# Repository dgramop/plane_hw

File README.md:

# Plane Hardware

Board Design Rev1 Mistakes:
- Wrong footprint for the PX4 connector on the pitot. Accidentally used the same one as all the I2C busses. Already have these connectors
- Forgot to order MALE connectors that go on the board. JST female is the for the cable. Whoops

Rev 2 Wishlist:
- Better harnessing - fewer things to connect + better modularity. Then we can have test beds for each part in isolation

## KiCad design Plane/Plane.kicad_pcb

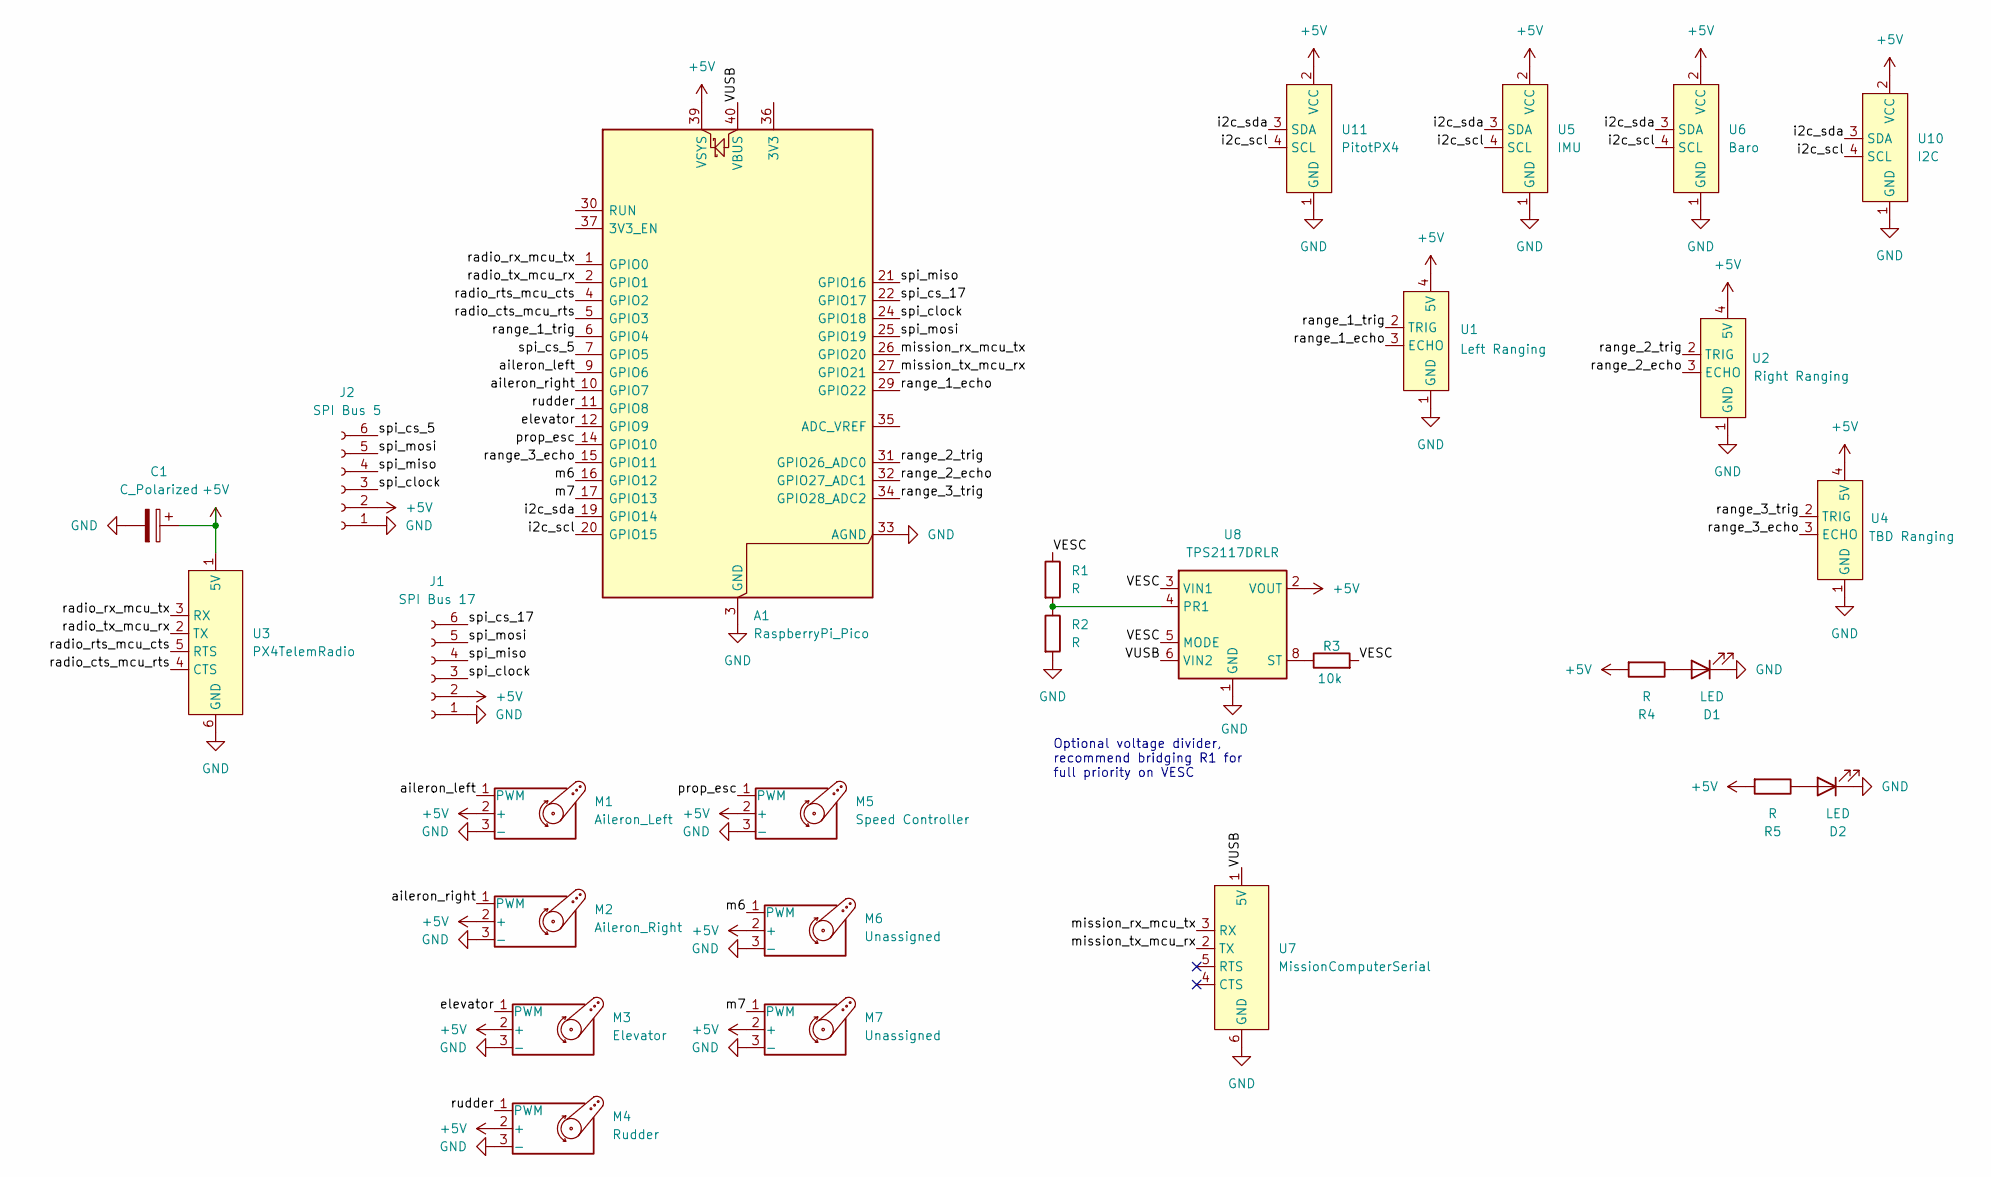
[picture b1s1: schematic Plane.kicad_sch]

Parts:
A1: RaspberryPi_Pico; RaspberryPi_Pico_Common_Unspecified
C1: C_Polarized; CP_Radial_D6.3mm_P2.50mm
D1, D2: LED; JST_PH_B2B-PH-K_1x02_P2.00mm_Vertical
J1: SPI Bus 17; JST_PH_B6B-PH-K_1x06_P2.00mm_Vertical
J2: SPI Bus 5; JST_PH_B6B-PH-K_1x06_P2.00mm_Vertical
M1: Aileron_Left; JST_PH_B3B-PH-K_1x03_P2.00mm_Vertical
M2: Aileron_Right; JST_PH_B3B-PH-K_1x03_P2.00mm_Vertical
M3: Elevator; JST_PH_B3B-PH-K_1x03_P2.00mm_Vertical
M4: Rudder; JST_PH_B3B-PH-K_1x03_P2.00mm_Vertical
M5: Speed Controller; JST_PH_B3B-PH-K_1x03_P2.00mm_Vertical
M6, M7: Unassigned; JST_PH_B3B-PH-K_1x03_P2.00mm_Vertical
R1, R2, R4, R5: R; R_0805_2012Metric_Pad1.20x1.40mm_HandSolder
R3: 10k; R_0805_2012Metric_Pad1.20x1.40mm_HandSolder
U1: Left Ranging; JST_PH_B4B-PH-K_1x04_P2.00mm_Vertical
U2: Right Ranging; JST_PH_B4B-PH-K_1x04_P2.00mm_Vertical
U3: PX4TelemRadio; JST_GH_SM06B-GHS-TB_1x06-1MP_P1.25mm_Horizontal
U4: TBD Ranging; JST_PH_B4B-PH-K_1x04_P2.00mm_Vertical
U5: IMU; JST_PH_B4B-PH-K_1x04_P2.00mm_Vertical
U6: Baro; JST_PH_B4B-PH-K_1x04_P2.00mm_Vertical
U7: MissionComputerSerial; JST_GH_SM06B-GHS-TB_1x06-1MP_P1.25mm_Horizontal
U8: TPS2117DRLR; SOT-583-8
U10: I2C; JST_PH_B4B-PH-K_1x04_P2.00mm_Vertical
U11: PitotPX4; JST_PH_B4B-PH-K_1x04_P2.00mm_Vertical

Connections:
+5V: A1.39 (VSYS), C1.1, J1.2, J2.2, M1.2 (+), M2.2 (+), M3.2 (+), M4.2 (+), M5.2 (+), M6.2 (+), M7.2 (+), R4.2, R5.2, U1.4 (5V), U2.4 (5V), U3.1 (5V), U4.4 (5V), U5.2 (VCC), U6.2 (VCC), U8.2 (VOUT), U8.7 (VOUT), U10.2 (VCC), U11.2 (VCC)
/VESC: R1.1, R3.2, U8.3 (VIN1), U8.5 (MODE)
/VUSB: A1.40 (VBUS), U7.1 (5V), U8.6 (VIN2)
/aileron_left: A1.9 (GPIO6), M1.1 (PWM)
/aileron_right: A1.10 (GPIO7), M2.1 (PWM)
/elevator: A1.12 (GPIO9), M3.1 (PWM)
/i2c_scl: A1.20 (GPIO15), U5.4 (SCL), U6.4 (SCL), U10.4 (SCL), U11.4 (SCL)
/i2c_sda: A1.19 (GPIO14), U5.3 (SDA), U6.3 (SDA), U10.3 (SDA), U11.3 (SDA)
/m6: A1.16 (GPIO12), M6.1 (PWM)
/m7: A1.17 (GPIO13), M7.1 (PWM)
/mission_rx_mcu_tx: A1.26 (GPIO20), U7.3 (RX)
/mission_tx_mcu_rx: A1.27 (GPIO21), U7.2 (TX)
/prop_esc: A1.14 (GPIO10), M5.1 (PWM)
/radio_cts_mcu_rts: A1.5 (GPIO3), U3.4 (CTS)
/radio_rts_mcu_cts: A1.4 (GPIO2), U3.5 (RTS)
/radio_rx_mcu_tx: A1.1 (GPIO0), U3.3 (RX)
/radio_tx_mcu_rx: A1.2 (GPIO1), U3.2 (TX)
/range_1_echo: A1.29 (GPIO22), U1.3 (ECHO)
/range_1_trig: A1.6 (GPIO4), U1.2 (TRIG)
/range_2_echo: A1.32 (GPIO27_ADC1), U2.3 (ECHO)
/range_2_trig: A1.31 (GPIO26_ADC0), U2.2 (TRIG)
/range_3_echo: A1.15 (GPIO11), U4.3 (ECHO)
/range_3_trig: A1.34 (GPIO28_ADC2), U4.2 (TRIG)
/rudder: A1.11 (GPIO8), M4.1 (PWM)
/spi_clock: A1.24 (GPIO18), J1.3, J2.3
/spi_cs_5: A1.7 (GPIO5), J2.6
/spi_cs_17: A1.22 (GPIO17), J1.6
/spi_miso: A1.21 (GPIO16), J1.4, J2.4
/spi_mosi: A1.25 (GPIO19), J1.5, J2.5
GND: A1.3 (GND), A1.8 (GND), A1.13 (GND), A1.18 (GND), A1.23 (GND), A1.28 (GND), A1.33 (AGND), A1.38 (GND), C1.2, D1.1 (K), D2.1 (K), J1.1, J2.1, M1.3 (-), M2.3 (-), M3.3 (-), M4.3 (-), M5.3 (-), M6.3 (-), M7.3 (-), R2.2, U1.1 (GND), U2.1 (GND), U3.6 (GND), U4.1 (GND), U5.1 (GND), U6.1 (GND), U7.6 (GND), U8.1 (GND), U10.1 (GND), U11.1 (GND)
unnamed: D1.2 (A), R4.1
unnamed: D2.2 (A), R5.1
unnamed: R1.2, R2.1, U8.4 (PR1)
unnamed: R3.1, U8.8 (ST)

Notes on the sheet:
Optional voltage divider, recommend bridging R1 for full priority on VESC

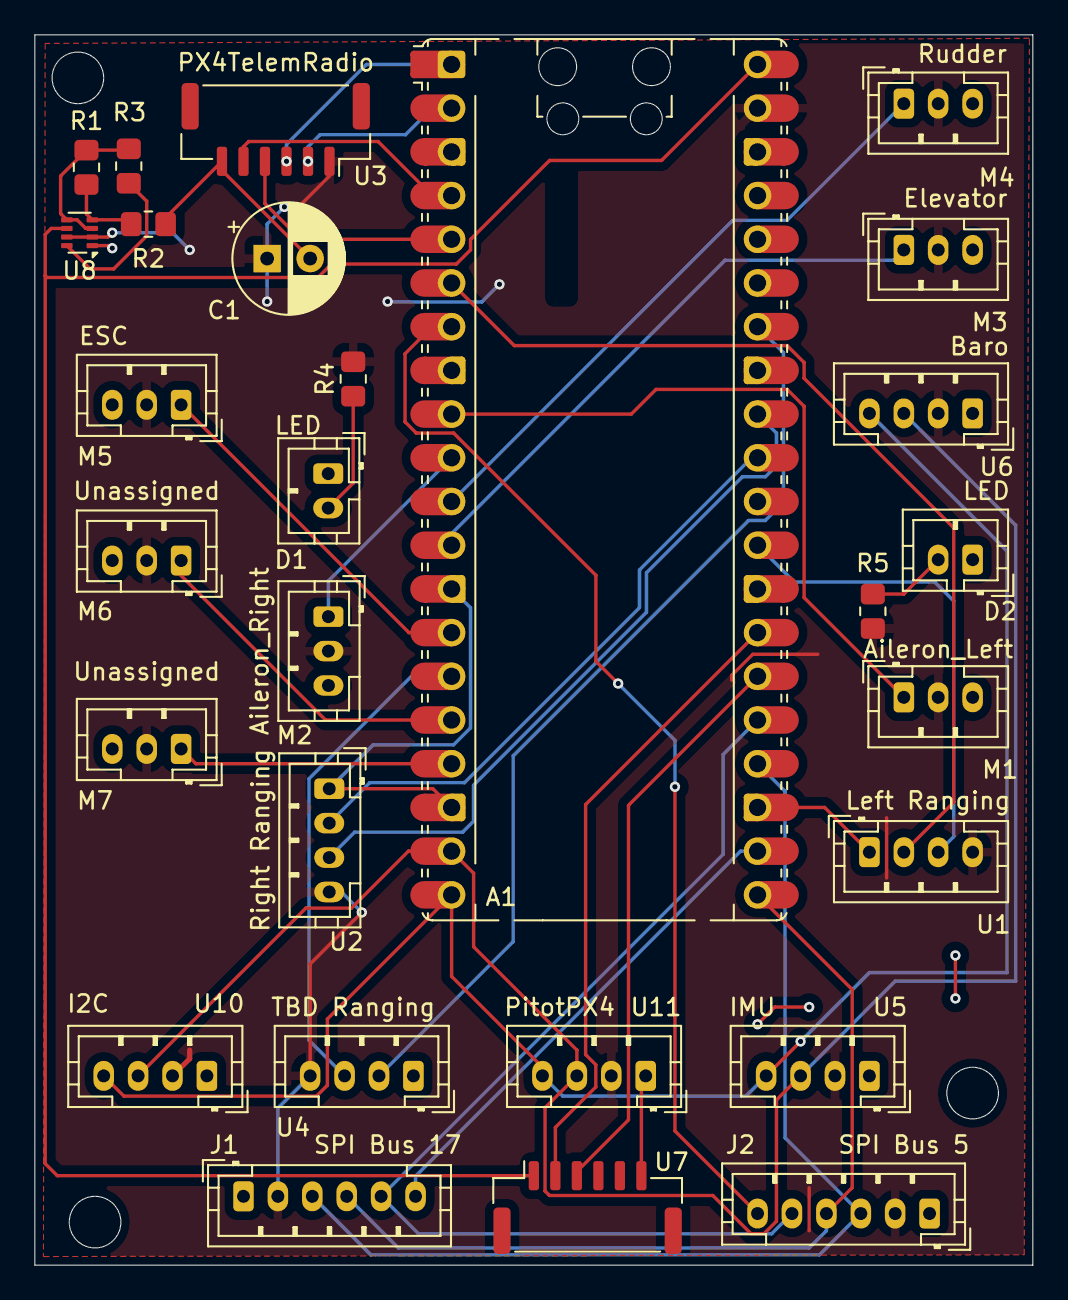
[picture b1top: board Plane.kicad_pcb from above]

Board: 2 copper layers, 58.0 x 71.5 mm, 28 parts (0 on the bottom side), 34 nets.

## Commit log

2025-03-24 hw and elec
2025-03-25 schematic
2025-03-25 autosave removal
2025-03-26 fix some mistakes and connect power mux
2025-03-26 init board
2025-03-27 swap resistors to 0805, move stuff around
2025-04-19 design 1
2025-04-19 finish routing
2025-04-19 oredered last night
